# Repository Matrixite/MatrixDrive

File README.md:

# MatrixDrive

MatrixDrive started with a simple idea: make a Mega Drive/Genesis cartridge
that you can plug into a computer with USB-C, copy a game onto like a flash
drive, and then use in a real console.

Revision B takes that idea quite a bit further. It is also designed to run
Master System software on compatible Mega Drive hardware, supply ROM data to a
real 32X, work in the upper slot of Sonic & Knuckles, and keep supported save
data in battery-free FRAM.

- [Download the current source and prebuilt firmware package](https://github.com/Matrixite/MatrixDrive/raw/refs/heads/main/MatrixDrive_Dual_System_Cart_RevB_LockOn_Codemasters_64K_FRAM.zip)
- [Download the standalone KiCad project](https://github.com/Matrixite/MatrixDrive/raw/refs/heads/main/MatrixDrive_RevB_KiCad_Project.zip)

> [!IMPORTANT]
> MatrixDrive is still an engineering prototype. The software and logic have
> been tested, and the PCB has a preliminary fully connected route, but no
> physical cartridge has been built or tested in a console. Several package pin
> assignments still need to be verified and the board has not passed KiCad DRC.
> Please do not send the current PCB straight to a manufacturer.

## What MatrixDrive can do

| Mode | Files | Maximum size | What happens |
| --- | --- | ---: | --- |
| Mega Drive / Genesis | `.BIN`, `.MD`, `.GEN` | 4 MiB | The game is presented as linear cartridge ROM |
| 32X with real 32X hardware | `.32X` | 4 MiB | MatrixDrive supplies the ROM while the real 32X provides the 32X hardware |
| Sonic & Knuckles upper slot | Mega Drive images | 2 MiB recommended | Supports Sonic 2 lock-on and Sonic 3 with its dedicated save area |
| Master System | `.SMS` | 2 MiB | Uses either the Sega or Codemasters mapper selected by SW4 |

Master System mode should work on standard Mega Drive/Genesis Model 1 and Model
2 consoles. It will not work on an unmodified Genesis 3 or Sega Nomad because
their cartridge-port Master System mode pin is disconnected. The JVC X'Eye can
run SMS cartridges through an adapter, but its reset circuit prevents SMS games
from running from a Genesis flash cartridge such as MatrixDrive. Compatibility
with other all-in-one, portable, licensed, or clone systems has not yet been
verified. MatrixDrive also does not fit a standalone Master System cartridge
slot, and SMS mode cannot run through a 32X or the Sonic & Knuckles upper slot.

## How it works

When MatrixDrive is connected to a computer, it appears as a FAT16 drive called
`MATRIXDRV`. The RP2350B checks the game image and programs it into parallel NOR
flash. After USB is disconnected, the CPLD takes over and responds to the
console immediately, without waiting for the microcontroller to boot.

The main hardware is:

- an RP2350B for USB, file handling, validation, and flash programming;
- 32-Mbit x16 parallel NOR flash for predictable cartridge ROM reads;
- an ATF1508ASV CPLD for mode selection, address decoding, and SMS mapping;
- level translators and bus isolation for the 5 V console and 3.3 V logic;
- two FRAM devices providing 64 KiB of battery-free SMS save storage;
- a separate FRAM for the 8 KiB Sonic 3 lock-on save window;
- USB/console power isolation, status LEDs, SWD/UART, and test points.

## Loading a game

1. Remove MatrixDrive from the console, 32X, or lock-on cartridge.
2. Connect it to your computer with USB-C.
3. Open the `MATRIXDRV` drive, delete the old game, and copy over one supported
   image.
4. Safely eject the drive and wait for the green completion light.
5. Disconnect USB completely.
6. With all power off, select MD or SMS with SW2 and choose the required profile
   with SW4.
7. Insert the cartridge, then power on the console.

> [!WARNING]
> Never connect USB while MatrixDrive is fitted to a console, 32X, or Sonic &
> Knuckles cartridge. Never move SW2 or SW4 while powered, and never hot-plug any
> part of the cartridge stack.

## Switch settings

SW4 changes purpose depending on the position of SW2:

| SW2 | SW4 low | SW4 high |
| --- | --- | --- |
| MD | Linear ROM, 32X, or Sonic 2 lock-on | Linear ROM with Sonic 3 save FRAM |
| SMS | Sega mapper | Codemasters mapper |

Always change these switches with USB and console power disconnected.

## Sonic & Knuckles lock-on

For **Sonic 2 & Knuckles**, copy a normal Sonic 2 image, set SW2 to **MD**, and
set SW4 low to **LINEAR**. Power-of-two images up to 2 MiB are mirrored across
the upper-cartridge ROM window.

For **Sonic 3 & Knuckles**, copy a normal Sonic 3 image, set SW2 to **MD**, and
set SW4 high to **S3 SAVE**. MatrixDrive then maps the dedicated save FRAM over
odd-byte addresses `$200001-$203FFF` while leaving the rest of the ROM visible.

Read [Sonic & Knuckles lock-on mode](MatrixDrive_Dual_System_Cart_RevB/docs/sonic-knuckles-lock-on.md)
for the exact mapping, switch positions, and physical-fit checks.

## Using a real 32X

MatrixDrive is not trying to reproduce a 32X. A real 32X still supplies its
processors, boot ROM, registers, video, and audio hardware; MatrixDrive only
supplies the cartridge ROM.

Copy a `.32X` image, set SW2 to **MD**, leave SW4 low, disconnect USB, and fit
MatrixDrive to an unpowered 32X. The installer checks the `SEGA` header and
`MARS CHECK MODE` marker before accepting the image.

Do not use SW4 high for 32X software because that setting deliberately replaces
part of the ROM address range with the Sonic 3 save window. More detail is in
[32X cartridge mode](MatrixDrive_Dual_System_Cart_RevB/docs/32x-mode.md).

## Master System mapping and saves

| Profile | Mapper writes | Starting ROM banks | Save window |
| --- | --- | --- | --- |
| Sega | `$FFFC-$FFFF` | 0, 1, 2 | 16 KiB at `$8000-$BFFF` |
| Codemasters | `$0000`, `$4000`, `$8000` | 0, 1, 0 | 8 KiB at `$A000-$BFFF` |

In Codemasters mode, bit 7 of the `$4000` write enables FRAM and bits 2:0 choose
one of eight 8 KiB banks. This makes all 64 KiB of SMS save storage available
without hiding the ROM at `$8000-$9FFF`.

See [Master System mode](MatrixDrive_Dual_System_Cart_RevB/docs/master-system-mode.md)
for the full register and banking behaviour.

## Supported image rules

- Mega Drive/Genesis images must be normal big-endian ROMs, contain `SEGA` at
  offset `0x100`, and fit within 4 MiB.
- 32X images must use `.32X`, contain `SEGA` at `0x100` and `MARS CHECK MODE` at
  `0x3C0`, be a multiple of four bytes, and fit within 4 MiB.
- Lock-on images should be even-sized powers of two no larger than 2 MiB.
- Headerless SMS images need `TMR SEGA` at `0x1FF0`, `0x3FF0`, or `0x7FF0`.
- Interleaved `.SMD` files and copier headers are not supported.
- Only use game images that you are legally entitled to use.

No commercial ROM images are included in this repository.

## What has been tested

The project is automatically rebuilt and tested on every change. The passing
software-only tests currently cover:

- the FAT16 USB drive and ROM installer;
- Mega Drive, Master System, and 32X image validation;
- simulated NOR programming and ROM mirroring;
- Sega and Codemasters SMS mapper behaviour;
- Codemasters FRAM enabling and all eight save banks;
- Sonic 2/Sonic 3 lock-on mapping and the Sonic 3 save decoder;
- CPLD RTL simulation for MD, SMS, 32X ROM access, and lock-on modes;
- a complete RP2350B firmware build;
- a two-ROM emulator test that reached the combined Sonic 3 & Knuckles title
  screen and opening sequence.

These tests show that the intended software and logic paths behave correctly.
They cannot prove cartridge fit, signal timing, voltage translation, power
isolation, save retention, or operation on real Sega hardware.

## PCB status

The KiCad project contains a complete logical schematic and a preliminary
eight-layer PCB route. The routing report currently records all 188 routable
nets connected, using six signal layers plus dedicated ground and 3.3 V planes.

Before a board can be considered ready to build, it still needs:

- verified physical pin assignments and manufacturer footprints for the
  RP2350B, CPLD, NOR, translators, and FRAM devices;
- CPLD fitting, resource checks, and worst-case timing analysis;
- KiCad ERC/DRC after refilling the copper zones;
- USB differential-pair and signal/power-integrity review;
- cartridge-edge, PCB-thickness, bevel, shell, and insertion measurements;
- staged bench testing before it is connected to any console.

Only the Sonic 3 odd-byte save layout is implemented for Mega Drive software.
Generic Mega Drive or 32X SRAM/EEPROM saves, ROMs larger than 4 MiB,
enhancement hardware, unusual regional or game-specific SMS mappers, light-gun
support, and Sega mapper RAM-at-`$C000` mode are outside this revision.

Start with [Safety and bring-up](MatrixDrive_Dual_System_Cart_RevB/docs/safety-and-bringup.md)
before attempting any hardware test.

## Project layout

| Path | What you will find there |
| --- | --- |
| [`MatrixDrive_Dual_System_Cart_RevB/`](MatrixDrive_Dual_System_Cart_RevB/) | Main Revision B project |
| [`cpld/`](MatrixDrive_Dual_System_Cart_RevB/cpld/) | Mapper RTL, reference model, and testbench |
| [`firmware/`](MatrixDrive_Dual_System_Cart_RevB/firmware/) | RP2350B USB installer firmware |
| [`hardware/`](MatrixDrive_Dual_System_Cart_RevB/hardware/) | KiCad files, BOM, pinout, netlist, and routing report |
| [`docs/`](MatrixDrive_Dual_System_Cart_RevB/docs/) | Architecture, compatibility, and bring-up notes |
| [`tools/`](MatrixDrive_Dual_System_Cart_RevB/tools/) | Project generator, router, and validation scripts |

The [full design README](MatrixDrive_Dual_System_Cart_RevB/README.md) contains
the component-level details and additional design notes.

## Building and testing the project

You will need Python 3, the Raspberry Pi Pico SDK 2.3.0, an Arm GNU toolchain,
CMake/Ninja, and Icarus Verilog.

```sh
cd MatrixDrive_Dual_System_Cart_RevB
python3 tools/generate_kicad_project.py
python3 tools/route_kicad_pcb.py
python3 tools/validate_project.py
```

To build the RP2350B firmware:

```sh
export PICO_SDK_PATH=/absolute/path/to/pico-sdk
cmake -S firmware -B ../build/firmware -G Ninja \
  -DPICO_BOARD=matrixdrive \
  -DPICO_PLATFORM=rp2350-arm-s \
  -DCMAKE_BUILD_TYPE=Release
cmake --build ../build/firmware
```

## Technical references

- [Genesis Plus GX cartridge implementation](https://github.com/ekeeke/Genesis-Plus-GX/blob/master/core/cart_hw/md_cart.c)
- [Sega 32X Hardware Manual transcription](https://github.com/matiaszanolli/sega-vr-disasm/blob/master/docs/32x-hardware-manual.md)
- [Raspberry Pi RP2350 documentation](https://www.raspberrypi.com/documentation/microcontrollers/microcontroller-chips.html)
- [Microchip ATF1508ASV](https://www.microchip.com/en-us/product/atf1508asv)
- [Infineon FM18W08 FRAM](https://www.infineon.com/part/FM18W08-SG)
- [TI SN74LVC1T45](https://www.ti.com/product/SN74LVC1T45)

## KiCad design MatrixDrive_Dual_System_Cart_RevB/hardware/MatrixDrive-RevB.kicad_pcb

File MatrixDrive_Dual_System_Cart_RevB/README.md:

# MatrixDrive Dual-System USB Cartridge — Revision B

MatrixDrive Revision B is a prototype USB-loadable Mega Drive/Genesis cartridge that can also supply ROM to a real 32X, run Master System software on compatible consoles, and act as the upper cartridge in Sonic & Knuckles lock-on mode. USB-C exposes a removable FAT16 drive named `MATRIXDRV`; after one ROM is copied and safely ejected, the RP2350B installs it into non-volatile parallel NOR.

Console reads never depend on RP2350 response time. Translators and an instant-on CPLD connect the console directly to NOR or the selected FRAM.

## Supported images

| Console mode | File | Active image limit | Cartridge hardware |
| --- | --- | ---: | --- |
| Mega Drive / Genesis | `.BIN`, `.MD`, `.GEN` | 4 MiB | Linear `$000000-$3FFFFF` ROM |
| 32X through a real 32X | `.32X` | 4 MiB | Linear x16 ROM with 4 MiB mask-ROM-style mirroring |
| Sonic & Knuckles upper slot | Mega Drive image | 2 MiB recommended | Mirrored ROM; optional Sonic 3 save profile |
| Master System | `.SMS` | 2 MiB | Sega or Codemasters mapper selected by SW4 |

Power-of-two Mega Drive images smaller than 2 MiB are repeated by the installer through the full 2 MiB lock-on window. This gives a 1 MiB Sonic 2 image the mirroring expected from its original mask ROM.

Power-of-two `.32X` images smaller than 4 MiB are repeated through the complete 32-Mbit cartridge space. The firmware requires the standard `SEGA` header at `0x100` and `MARS CHECK MODE` at `0x3C0`, then preserves every ROM byte—including the mandatory 32X security/startup area beginning at `0x3F0`.

For Sonic 3 & Knuckles, SW4's high position in MD mode enables a dedicated 8 KiB odd-byte FRAM window at `$200001-$203FFF`. This storage is physically separate from the two FM18W08 devices that supply the complete 64 KiB SMS save array.

SMS images are stored one byte per x16 NOR word. The CPLD implements Sega or Codemasters 16 KiB banking selected by SW4. Plain 8/16/32/48 KiB images and larger mapped images work.

## Normal use

1. Remove MatrixDrive from the console, 32X, or Sonic & Knuckles cartridge.
2. Connect USB-C, remove the previous image, and copy one supported ROM to `MATRIXDRV`.
3. Safely eject and wait for the steady green completion indication.
4. Disconnect USB and set SW2/SW4 while all hardware is unpowered.
5. Insert MatrixDrive directly into the console, into the real 32X cartridge slot for `.32X` use, or into the Sonic & Knuckles upper slot for MD lock-on use.
6. Power on. In SMS mode, use the cartridge PAUSE button when a game needs the Master System NMI pause input.

### Switch positions

| Use | SW2 | SW4 |
| --- | --- | --- |
| Normal Mega Drive or Sonic 2 & Knuckles | MD | Low: LINEAR |
| 32X cartridge through real 32X hardware | MD | Low: LINEAR |
| Sonic 3 & Knuckles with saves | MD | High: S3 SAVE |
| Sega-mapper SMS | SMS | Low: SEGA |
| Codemasters-mapper SMS | SMS | High: CODEMASTERS |

Never move either switch while powered. Never connect USB while MatrixDrive is inserted into a console, 32X, or another cartridge.

## 32X compatibility

MatrixDrive does not emulate a 32X. In this mode, the physical 32X supplies its dual SH2 processors, boot ROM, registers, video and audio hardware, while MatrixDrive behaves as the attached 4 MiB cartridge ROM. The 32X adapter performs its normal cartridge banking internally.

Use SW2=MD and SW4=LINEAR. SW4's S3 SAVE position is not compatible because it intentionally replaces odd-byte addresses `$200001-$203FFF` with FRAM. Generic 32X SRAM/EEPROM saves, images larger than 4 MiB, and special cartridge hardware are not implemented.

See `docs/32x-mode.md` for exact mapping and real-hardware bring-up requirements.

## Lock-on compatibility

The electrical profile follows the documented lock-on behaviour and the Genesis Plus GX implementation:

- Sonic & Knuckles supplies its own ROM at the lower 2 MiB and exposes the upper cartridge in the remaining window.
- MatrixDrive behaves as a normal MD ROM in the upper slot.
- The installer supplies mask-ROM-style mirroring for even-sized power-of-two images up to 2 MiB.
- The Sonic 3 save profile maps U20 to odd-byte addresses `$200001-$203FFF`.
- U19 translates the CPLD's high-byte-disable request into the 5 V domain so U7 is inactive during low-byte-only save cycles.
- Sonic & Knuckles owns its `$A130F0` lock-on control; MatrixDrive does not emulate the base lock-on cartridge.

See `docs/sonic-knuckles-lock-on.md` for exact use and remaining physical-fit validation.

## Image validation

- Mega Drive images require `SEGA` at byte offset `0x100`, normal big-endian byte order, and a maximum size of 4 MiB. Interleaved `.SMD` images are rejected.
- `.32X` images must be a multiple of four bytes, fit in 4 MiB, contain `SEGA` at `0x100`, and contain `MARS CHECK MODE` at `0x3C0`.
- Lock-on images should be even-sized powers of two no larger than 2 MiB.
- Headerless SMS images require `TMR SEGA` at `0x1FF0`, `0x3FF0`, or `0x7FF0`.
- Use only software you are legally entitled to use.

## Hardware summary

- RP2350B, USB Full-Speed Mass Storage, and a 16 MiB FAT16 staging flash.
- S29GL032N-compatible 32-Mbit x16 active parallel NOR.
- ATF1508ASV-15AU100 CPLD for instant-on mode, SMS mapping, and Sonic 3 save decode.
- U17/U18: two FM18W08 32 KiB x8 FRAMs, exactly 64 KiB for SMS saves.
- U20: dedicated FM18W08, with 8 KiB decoded for Sonic 3 lock-on saves.
- U19: SN74LVC1T45 translating the MD high-data-disable control to CART_5V.
- Dual-supply 5 V/3.3 V translation on every active cartridge signal.
- USB/console source isolation, PROGRAM and PAUSE buttons, and power-off selectors.

## Project contents

- `docs/architecture.md` — electrical and data-path architecture.
- `docs/master-system-mode.md` — SMS mapper and storage details.
- `docs/32x-mode.md` — real-32X cartridge mapping, switches, limits, and bring-up.
- `docs/sonic-knuckles-lock-on.md` — lock-on mapping, switches, fit, and limitations.
- `docs/safety-and-bringup.md` — mandatory staged test procedure.
- `hardware/bom.csv`, `connector-pinout.csv`, `electrical-netlist.csv` — connection authorities.
- `hardware/MatrixDrive-RevB.sch` — complete logical schematic; KiCad 8/9 converts it to native format on first save.
- `hardware/MatrixDrive-RevB.kicad_pcb` — native preliminary routed eight-layer PCB with the physical cartridge edge, six signal layers, and dedicated ground/3.3 V planes.
- `hardware/routing-report.json` — deterministic route completion counts, layer assignment, widths, and via dimensions.
- `hardware/README-KICAD.md` — project opening instructions and fabrication release gates.
- `cpld/matrixdrive_mapper.v` — synthesizable SMS and lock-on decoder RTL.
- `cpld/test_matrixdrive_mapper.v` — RTL mapper/FRAM testbench.
- `firmware/` — RP2350/Pico SDK firmware source.

## Engineering status

This is a **Revision B engineering prototype**, not a fabrication-ready or production-tested commercial cartridge. The PCB has a preliminary connectivity-complete route, but it has not passed KiCad DRC or physical review. Before fabrication, review and verify the logical schematic, assign and fit the CPLD, verify resources and timing, copy the official RP2350B minimal design, confirm exact package pin maps, review/refine the route, pass ERC/DRC, and measure the edge/shell against a normal donor cartridge, a real 32X cartridge slot, and a real Sonic & Knuckles upper slot.

Do not send the included KiCad PCB directly to fabrication. Complete the release gates in `hardware/README-KICAD.md` and `docs/safety-and-bringup.md` before any console test.

The repository root also contains `MatrixDrive_RevB_KiCad_Project.zip`, a
standalone copy of the schematic, board, symbol library, BOM and connection
authorities.

## Build prerequisites

- Raspberry Pi Pico SDK 2.3.0 and Arm GNU Toolchain.
- CMake plus Ninja or Make.
- Icarus Verilog for RTL simulation.
- KiCad 8 or later for schematic conversion, PCB editing, ERC and DRC.
- A verified ATF1508ASV fitting/JED programming flow.

The prototype USB descriptor uses TinyUSB's development VID `0xCAFE`. Obtain a proper VID/PID before distribution.

## Primary references

- Genesis Plus GX MD cartridge: <https://github.com/ekeeke/Genesis-Plus-GX/blob/master/core/cart_hw/md_cart.c>
- Genesis Plus GX SRAM: <https://github.com/ekeeke/Genesis-Plus-GX/blob/master/core/cart_hw/sram.c>
- Sega 32X Hardware Manual transcription: <https://github.com/matiaszanolli/sega-vr-disasm/blob/master/docs/32x-hardware-manual.md>
- TI SN74LVC1T45: <https://www.ti.com/product/SN74LVC1T45>
- RP2350: <https://www.raspberrypi.com/documentation/microcontrollers/microcontroller-chips.html>
- ATF1508ASV: <https://www.microchip.com/en-us/product/atf1508asv>
- FM18W08 FRAM: <https://www.infineon.com/part/FM18W08-SG>

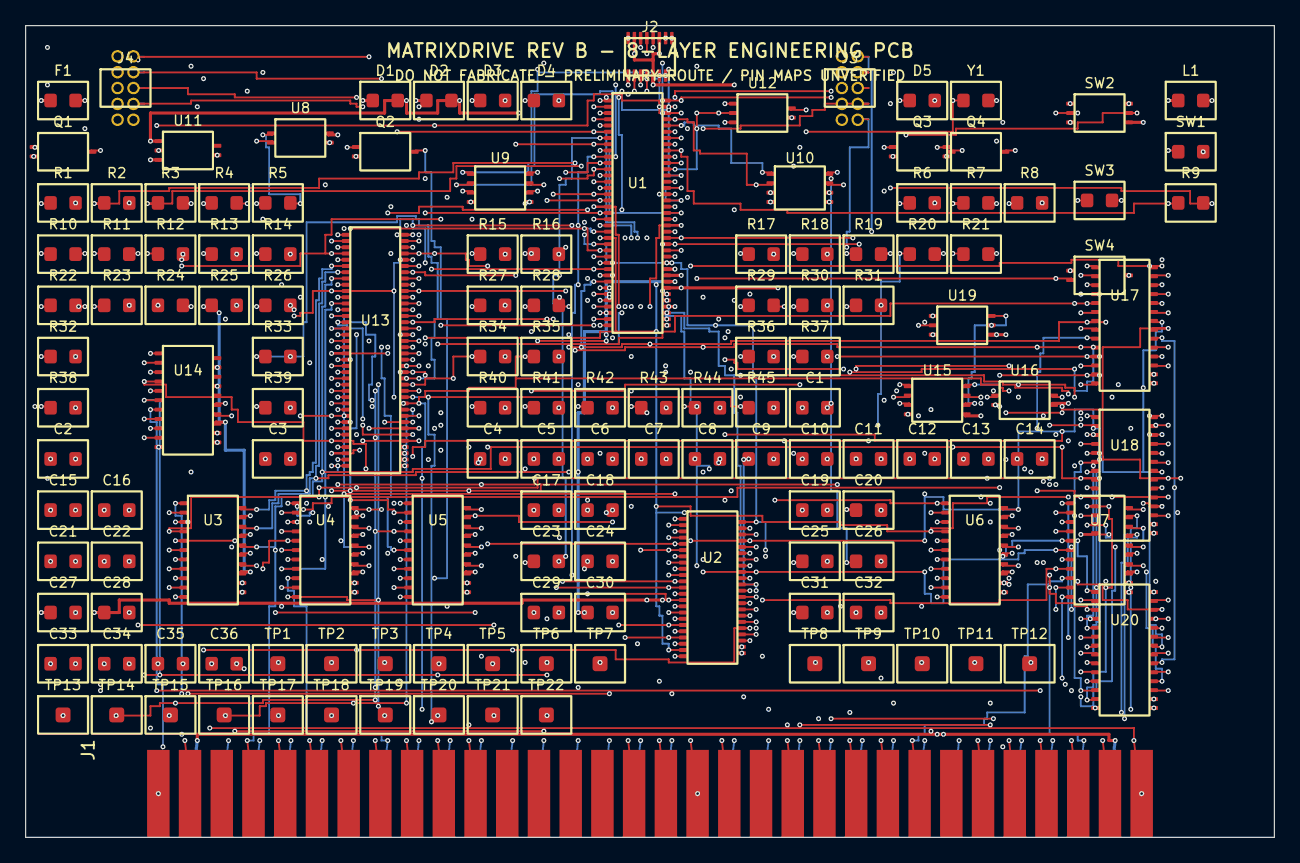
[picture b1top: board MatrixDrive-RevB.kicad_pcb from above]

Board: 8 copper layers, 100.0 x 65.0 mm, 143 parts (0 on the bottom side), 190 nets.

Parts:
C1, C2, C3, C4, C5, C6, C7, C8, C9, C10, C11, C12, C13, C14, C15, C16, C17, C18, C34, C35, C36: 100nF; 0603
C19, C20, C21, C22: 1uF; 0603
C23, C24: 10uF; 0805
C25, C26: 15pF; 0402
C27: 4.7uF; 0603
C28, C29, C30, C31, C32, C33: TBD_REF; 0402
D1, D2: PMEG2010AEB; SOD_523
D3: GREEN_LED; 0603_LED
D4: AMBER_LED; 0603_LED
D5: RED_LED; 0603_LED
F1: MF-MSMF020-2; 1812
J1: MEGA_DRIVE_EDGE; MD_2x32_EDGE
J2: USB4105-GF-A; USB_C_16P
J3: SWD_UART_2x5 DNP; HDR_2x5_1_27
J4: CPLD_JTAG_2x5; HDR_2x5_1_27
L1: 3.3uH; 2016
Q1, Q2, Q3, Q4: 2N7002; SOT_23
R1, R2: 5.1k; 0603
R3, R4: 27R; 0603
R5, R12, R19, R20, R21, R22, R23, R25, R26, R27, R31, R32, R33, R34, R35, R36, R42, R43, R45: 10k; 0603
R6, R7, R8, R14, R29, R30, R37, R38, R39, R40, R41, R44: 100k; 0603
R9, R10, R11, R28: 1k; 0603
R13: 0R; 0603
R15, R16, R17, R18: 10k DNP; 0603
R24: 33R; 0603
SW1: PROGRAM; SW_2P
SW2: MD_SMS_DPDT; SW_DPDT_6P
SW3: SMS_PAUSE; SW_2P
SW4: PROFILE_SPDT; SW_SPDT_3P
TP1: CART_5V; TP_SMD_1MM
TP2: USB_VBUS; TP_SMD_1MM
TP3: SYS_5V; TP_SMD_1MM
TP4: 3V3; TP_SMD_1MM
TP5: GND; TP_SMD_1MM
TP6: BUS_DISABLE; TP_SMD_1MM
TP7: SMS_MODE_3V3; TP_SMD_1MM
TP8: SMS_MODE_5V; TP_SMD_1MM
TP9: USB_MODE_3V3; TP_SMD_1MM
TP10: ROM_CE_N; TP_SMD_1MM
TP11: ROM_OE_N; TP_SMD_1MM
TP12: ROM_WE_N; TP_SMD_1MM
TP13: FRAM_CE_N; TP_SMD_1MM
TP14: FRAM_HI_CE_N; TP_SMD_1MM
TP15: FRAM_OE_N; TP_SMD_1MM
TP16: FRAM_WE_N; TP_SMD_1MM
TP17: MD_FRAM_CE_N; TP_SMD_1MM
TP18: MD_HIGH_DISABLE_3V3; TP_SMD_1MM
TP19: LWR_3V3; TP_SMD_1MM
TP20: UWR_3V3; TP_SMD_1MM
TP21: AS_3V3; TP_SMD_1MM
TP22: TIME_3V3; TP_SMD_1MM
U1: RP2350B; UNVERIFIED_LOGICAL_PACKAGE
U2: S29GL032N90TFI040; TSOP_I_48_UNVERIFIED_PINMAP
U3, U4, U5, U6, U7, U14: SN74LVC8T245PWR; TSSOP_24_LOGICAL
U8: SN74LVC1G17DBVR; SOT_23_5
U9: W25Q16JVSSIQ; SOIC_8
U10: W25Q128JVSIQ; SOIC_8
U11: TLV75533PDBVR; SOT_23_5
U12: TPD2EUSB30DRTR; DRT_9_LOGICAL
U13: ATF1508ASV-15AU100; TQFP_100_UNASSIGNED
U15: SN74LVC2G32DCUR; VSSOP_8
U16: SN74LVC1G04DBVR; SOT_23_5
U17, U18, U20: FM18W08-SG; SOIC_28_LOGICAL
U19: SN74LVC1T45DBVR; SOT_23_6
Y1: 12MHz_CRYSTAL; 3225_4P

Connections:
1V1: C27.1, C28.1, L1.2, U1.DVDD, U1.VREG_FB
3V3: C1.1, C2.1, C3.1, C4.1, C5.1, C6.1, C7.1, C8.1, C9.1, C10.1, C11.1, C12.1, C13.1, C14.1, C15.1, C16.1, C17.1, C18.1, C19.1, C21.1, C22.1, C24.1, C29.1, C32.1, C33.1, C34.1, C35.1, C36.1, J3.1, J4.1, R12.2, R24.1, R25.2, R26.2, R27.2, R31.2, R32.2, R34.2, R35.2, R36.2, R43.2, R45.2, SW2.3, SW4.3, TP4.1, U1.IOVDD_1, U1.IOVDD_2, U1.VREG_IN, U2.VCC, U3.VCCB, U4.VCCB, U5.VCCB, U6.VCCB, U7.VCCB, U9.8, U10.3, U10.7, U10.8, U11.5, U13.VCC_1, U13.VCC_2, U14.VCCB, U17.VDD, U18.VDD, U19.1, U19.5, U20.VDD
ADC_AVDD: C31.1, U1.ADC_AVDD
AS_3V3: TP21.1, U14.B4
AS_N: J1.B18, U14.A4
BOOT_QSPI_CS: U1.QSPI_CS, U9.1
BOOT_QSPI_IO0: U1.QSPI_SD0, U9.5
BOOT_QSPI_IO1: U1.QSPI_SD1, U9.2
BOOT_QSPI_IO2: U1.QSPI_SD2, U9.3
BOOT_QSPI_IO3: U1.QSPI_SD3, U9.7
BOOT_QSPI_SCK: U1.QSPI_SCLK, U9.6
BUS_DISABLE: R14.1, R15.1, R16.1, R17.1, R18.1, TP6.1, U3.OE_N, U4.OE_N, U5.OE_N, U6.OE_N, U8.Y, U14.OE_N, U15.1
CART_5V: C20.1, D1.1, F1.2, R19.2, R20.2, R21.2, R22.2, SW2.6, TP1.1, U3.VCCA, U4.VCCA, U5.VCCA, U6.VCCA, U7.VCCA, U8.VCC, U14.VCCA, U15.8, U16.5, U19.6
CART_5V_IN: F1.1, J1.A2, J1.A31
CART_A0: U3.B1, U13.CART_A0, U17.A0, U18.A0, U20.A0
CART_A1: U3.B2, U13.CART_A1, U17.A1, U18.A1, U20.A1
CART_A2: U3.B3, U13.CART_A2, U17.A2, U18.A2, U20.A2
CART_A3: U3.B4, U13.CART_A3, U17.A3, U18.A3, U20.A3
CART_A4: U3.B5, U13.CART_A4, U17.A4, U18.A4, U20.A4
CART_A5: U3.B6, U13.CART_A5, U17.A5, U18.A5, U20.A5
CART_A6: U3.B7, U13.CART_A6, U17.A6, U18.A6, U20.A6
CART_A7: U3.B8, U13.CART_A7, U17.A7, U18.A7, U20.A7
CART_A8: U4.B1, U13.CART_A8, U17.A8, U18.A8, U20.A8
CART_A9: U4.B2, U13.CART_A9, U17.A9, U18.A9, U20.A9
CART_A10: U4.B3, U13.CART_A10, U17.A10, U18.A10, U20.A10
CART_A11: U4.B4, U13.CART_A11, U17.A11, U18.A11, U20.A11
CART_A12: U4.B5, U13.CART_A12, U17.A12, U18.A12, U20.A12
CART_A13: U4.B6, U13.CART_A13
CART_A14: U4.B7, U13.CART_A14
CART_A15: U4.B8, U13.CART_A15
CART_A16: U5.B1, U13.CART_A16
CART_A17: U5.B2, U13.CART_A17
CART_A18: U5.B3, U13.CART_A18
CART_A19: U5.B4, U13.CART_A19
CART_A20: U5.B5, U13.CART_A20
CART_N: J1.B32, R13.1
CAS0_3V3: U5.B7, U13.CAS0_N
CAS0_N: J1.B16, U5.A7
CAS2_3V3: U5.B8, U13.CAS2_N
CAS2_N: J1.B21, U5.A8
CC1: J2.A5, R1.1
CC2: J2.B5, R2.1
CE0_3V3: U5.B6, U13.CE0_N
CE0_N: J1.B17, U5.A6
CPLD_TCK: J4.4, U13.TCK
CPLD_TDI: J4.8, U13.TDI
CPLD_TDO: J4.6, U13.TDO
CPLD_TMS: J4.2, U13.TMS
DATA_HIGH_BASE_DISABLE: U15.3, U15.6
DATA_HIGH_DISABLE: U7.OE_N, U15.5
FRAM_A13: R42.1, U13.FRAM_A13, U17.A13, U18.A13
FRAM_A14: R33.1, U13.FRAM_A14, U17.A14, U18.A14
FRAM_CE_N: R34.1, TP13.1, U13.FRAM_CE_N, U17.CE_N
FRAM_HI_CE_N: R43.1, TP14.1, U13.FRAM_HI_CE_N, U18.CE_N
FRAM_OE_N: R35.1, TP15.1, U13.FRAM_OE_N, U17.OE_N, U18.OE_N, U20.OE_N
FRAM_WE_N: R36.1, TP16.1, U13.FRAM_WE_N, U17.WE_N, U18.WE_N, U20.WE_N
GND: C1.2, C2.2, C3.2, C4.2, C5.2, C6.2, C7.2, C8.2, C9.2, C10.2, C11.2, C12.2, C13.2, C14.2, C15.2, C16.2, C17.2, C18.2, C19.2, C20.2, C21.2, C22.2, C23.2, C24.2, C25.2, C26.2, C27.2, C28.2, C29.2, C30.2, C31.2, C32.2, C33.2, C34.2, C35.2, C36.2, D3.2, D4.2, D5.2, J1.A1, J1.A18, J1.A32, J2.A1, J2.A12, J2.B1, J2.B12, J2.S1, J3.3, J3.5, J3.9, J4.3, J4.5, J4.9, Q1.2, Q2.2, Q3.2, Q4.2, R1.2, R2.2, R6.2, R8.2, R13.2, R14.2, R15.2, R16.2, R17.2, R18.2, R23.2, R30.2, R33.2, R37.2, R38.2, R39.2, R40.2, R41.2, R42.2, R44.2, SW1.2, SW2.1, SW2.4, SW4.1, TP5.1, U1.EP, U1.GND_1, U1.GND_2, U2.GND, U3.GND, U4.GND, U5.GND, U6.GND, U7.GND, U8.GND, U9.4, U10.4, U11.2, U12.GND, U13.GND_1, U13.GND_2, U14.A6, U14.A7, U14.A8, U14.GND, U15.4, U16.2, U17.VSS, U18.VSS, U19.3, U20.A13, U20.A14, U20.VSS
LED_AMBER: R10.1, U1.GPIO46
LED_AMBER_A: D4.1, R10.2
LED_GREEN: R9.1, U1.GPIO45
LED_GREEN_A: D3.1, R9.2
LED_RED: R11.1, U1.GPIO47
LED_RED_A: D5.1, R11.2
LOW_DATA_DIR: U6.DIR, U16.4
LWR_3V3: TP19.1, U13.LWR_N, U14.B1
LWR_N: J1.B28, U14.A1, U16.1
M3_N: J1.B30, Q1.3
MD_FRAM_CE_N: R45.1, TP17.1, U13.MD_FRAM_CE_N, U20.CE_N
MD_HIGH_DISABLE_3V3: TP18.1, U13.MD_HIGH_DISABLE, U19.2
MD_HIGH_DISABLE_5V: U15.7, U19.4
MEM_D0: U1.GPIO21, U2.DQ0, U6.B1, U13.DATA_IN0, U17.DQ0, U18.DQ0, U20.DQ0
MEM_D1: U1.GPIO22, U2.DQ1, U6.B2, U13.DATA_IN1, U17.DQ1, U18.DQ1, U20.DQ1
MEM_D2: U1.GPIO23, U2.DQ2, U6.B3, U13.DATA_IN2, U17.DQ2, U18.DQ2, U20.DQ2
MEM_D3: U1.GPIO24, U2.DQ3, U6.B4, U13.DATA_IN3, U17.DQ3, U18.DQ3, U20.DQ3
MEM_D4: U1.GPIO25, U2.DQ4, U6.B5, U13.DATA_IN4, U17.DQ4, U18.DQ4, U20.DQ4
MEM_D5: U1.GPIO26, U2.DQ5, U6.B6, U13.DATA_IN5, U17.DQ5, U18.DQ5, U20.DQ5
MEM_D6: U1.GPIO27, U2.DQ6, U6.B7, U13.DATA_IN6, U17.DQ6, U18.DQ6, U20.DQ6
MEM_D7: U1.GPIO28, U2.DQ7, U6.B8, U13.DATA_IN7, U17.DQ7, U18.DQ7, U20.DQ7
MEM_D8: U1.GPIO29, U2.DQ8, U7.B1
MEM_D9: U1.GPIO30, U2.DQ9, U7.B2
MEM_D10: U1.GPIO31, U2.DQ10, U7.B3
MEM_D11: U1.GPIO32, U2.DQ11, U7.B4
MEM_D12: U1.GPIO33, U2.DQ12, U7.B5
MEM_D13: U1.GPIO34, U2.DQ13, U7.B6
MEM_D14: U1.GPIO35, U2.DQ14, U7.B7
MEM_D15: U1.GPIO36, U2.DQ15, U7.B8
MRES_3V3: R41.1, U13.RESET_N, U14.B2
MRES_N: J1.B2, U14.A2
PAUSE_GATE: Q4.1, R40.1, SW3.2
ROM_A0: U1.GPIO0, U2.A0, U13.ROM_A0
ROM_A1: U1.GPIO1, U2.A1, U13.ROM_A1
ROM_A2: U1.GPIO2, U2.A2, U13.ROM_A2
ROM_A3: U1.GPIO3, U2.A3, U13.ROM_A3
ROM_A4: U1.GPIO4, U2.A4, U13.ROM_A4
ROM_A5: U1.GPIO5, U2.A5, U13.ROM_A5
ROM_A6: U1.GPIO6, U2.A6, U13.ROM_A6
ROM_A7: U1.GPIO7, U2.A7, U13.ROM_A7
ROM_A8: U1.GPIO8, U2.A8, U13.ROM_A8
ROM_A9: U1.GPIO9, U2.A9, U13.ROM_A9
ROM_A10: U1.GPIO10, U2.A10, U13.ROM_A10
ROM_A11: U1.GPIO11, U2.A11, U13.ROM_A11
ROM_A12: U1.GPIO12, U2.A12, U13.ROM_A12
ROM_A13: U1.GPIO13, U2.A13, U13.ROM_A13
ROM_A14: U1.GPIO14, U2.A14, U13.ROM_A14
ROM_A15: U1.GPIO15, U2.A15, U13.ROM_A15
ROM_A16: U1.GPIO16, U2.A16, U13.ROM_A16
ROM_A17: U1.GPIO17, U2.A17, U13.ROM_A17
ROM_A18: U1.GPIO18, U2.A18, U13.ROM_A18
ROM_A19: U1.GPIO19, U2.A19, U13.ROM_A19
ROM_A20: U1.GPIO20, U2.A20, U13.ROM_A20
ROM_BYTE_N: R27.1, U2.BYTE_N
ROM_CE_N: R31.1, TP10.1, U1.GPIO37, U2.CE_N, U13.ROM_CE_N
ROM_OE_N: R32.1, TP11.1, U1.GPIO38, U2.OE_N, U13.ROM_OE_N
ROM_RESET_N: R25.1, U2.RESET_N
ROM_WE_N: R12.1, TP12.1, U1.GPIO39, U2.WE_N
ROM_WP_N: R26.1, U2.WP_N
RUN_N: J3.6, U1.RUN
SMS_MAPPER_CM_3V3: R44.1, SW4.2, U13.CODEMASTERS
SMS_MODE_3V3: Q1.1, Q2.1, Q3.1, R37.1, R38.1, R39.1, SW2.2, SW3.1, TP7.1, U13.SMS_MODE
SMS_MODE_5V: SW2.5, TP8.1, U15.2
STAGE_CS_N: U1.GPIO41, U10.1
STAGE_MISO: U1.GPIO40, U10.2
STAGE_MOSI: U1.GPIO43, U10.5
STAGE_SCK: U1.GPIO42, U10.6
SWCLK: J3.4, U1.SWCLK
SWDIO: J3.2, U1.SWDIO
SYS_5V: C23.1, D1.2, D2.2, TP3.1, U11.1, U11.3
TIME_3V3: TP22.1, U14.B5
TIME_N: J1.B31, U14.A5
U3_DIR: R19.1, U3.DIR
U4_DIR: R20.1, U4.DIR
U5_DIR: R21.1, U5.DIR
U7_DIR: R23.1, U7.DIR
U14_DIR: R22.1, U14.DIR
UART_RX: J3.10, U1.UART_RX
UART_TX: J3.8, U1.UART_TX
USB_DM: J2.A7, J2.B7, R4.1, U12.IO2A
USB_DM_MCU: R4.2, U1.USB_DM, U12.IO2B
USB_DP: J2.A6, J2.B6, R3.1, U12.IO1A
USB_DP_MCU: R3.2, U1.USB_DP, U12.IO1B
USB_MODE_3V3: R29.2, R30.1, TP9.1, U13.USB_MODE
USB_PRESENT: R5.2, R6.1, U8.A
USB_SENSE_PROGRAM: R7.2, R8.1, SW1.1, U1.GPIO44
USB_VBUS: D2.1, J2.A4, J2.A9, J2.B4, J2.B9, R5.1, R7.1, R29.1, TP2.1
UWR_3V3: TP20.1, U14.B3
UWR_N: J1.B29, U14.A3
VA1: J1.A17, U3.A1
VA2: J1.A15, U3.A2
VA3: J1.A13, U3.A3
VA4: J1.A11, U3.A4
VA5: J1.A9, U3.A5
VA6: J1.A7, U3.A6
VA7: J1.A5, U3.A7
VA8: J1.A3, U3.A8
VA9: J1.B4, U4.A1
VA10: J1.B5, U4.A2
VA11: J1.A4, U4.A3
VA12: J1.A6, U4.A4
VA13: J1.A8, U4.A5
VA14: J1.A10, U4.A6
VA15: J1.A12, U4.A7
VA16: J1.A14, U4.A8
VA17: J1.A16, U5.A1
VA18: J1.B6, U5.A2
VA19: J1.B7, U5.A3
VA20: J1.B8, U5.A4
VA21: J1.B9, Q2.3, U5.A5
VA22: J1.B10, Q3.3
VA23_PAUSE: J1.B11, Q4.3
VD0: J1.A20, U6.A1
VD1: J1.A23, U6.A2
VD2: J1.A26, U6.A3
VD3: J1.A29, U6.A4
VD4: J1.A28, U6.A5
VD5: J1.A25, U6.A6
VD6: J1.A22, U6.A7
VD7: J1.A19, U6.A8
VD8: J1.A21, U7.A1
VD9: J1.A24, U7.A2
VD10: J1.A27, U7.A3
VD11: J1.A30, U7.A4
VD12: J1.B25, U7.A5
VD13: J1.B24, U7.A6
VD14: J1.B23, U7.A7
VD15: J1.B22, U7.A8
VREG_AVDD: C30.1, R24.2, U1.VREG_AVDD
VREG_SW: L1.1, U1.VREG_SW
XIN: R28.2, U1.XIN
XIN_XTAL: C25.1, R28.1, Y1.1
XOUT: C26.1, U1.XOUT, Y1.2

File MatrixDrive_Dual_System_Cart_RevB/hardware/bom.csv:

Reference,Quantity,Value or part,Description,Preferred footprint,Populate Rev B,Notes
U1,1,RP2350B,USB and flash controller,QFN-80-1EP 10x10mm,Yes,Use RP2350B for GPIO0-47
U2,1,S29GL032N90TFI040,32-Mbit 3V x16 parallel NOR,TSOP-I-48 18.4x12mm,Yes,90ns or faster; verify purchased package pinout
U3-U5,3,SN74LVC8T245PWR,Address and primary-control 5V-to-3V3 translators,TSSOP-24,Yes,DIR A to B
U6,1,SN74LVC8T245PWR,Low data byte bidirectional translator,TSSOP-24,Yes,DIR from U16 so SMS writes reach CPLD and FRAM
U7,1,SN74LVC8T245PWR,High data byte 3V3-to-5V translator,TSSOP-24,Yes,Disabled by U15 in SMS mode
U8,1,SN74LVC1G17DBVR,USB-present bus-disable buffer,SOT-23-5,Yes,Powered from CART_5V; require Ioff
U9,1,W25Q16JVSSIQ,2-MiB RP2350 QSPI boot flash,SOIC-8 5.3mm,Yes,Dedicated XIP device
U10,1,W25Q128JVSIQ,16-MiB USB staging SPI NOR,SOIC-8 5.3mm,Yes,Dedicated FAT16 volume
U11,1,TLV75533PDBVR,500mA 3.3V LDO,SOT-23-5,Yes,Input from SYS_5V
U12,1,TPD2EUSB30DRTR,USB D+/D- ESD protector,SOT-9/DRT,Yes,Place beside J2
U13,1,ATF1508ASV-15AU100,Instant-on SMS mapper and MD lock-on save decoder CPLD,TQFP-100 14x14mm,Yes,3.3V; fit/timing and pins are release gates
U14,1,SN74LVC8T245PWR,Secondary-control 5V-to-3V3 translator,TSSOP-24,Yes,Translates LWR MRES UWR AS and TIME
U15,1,SN74LVC2G32DCUR,Cascaded upper-data output-disable OR gates,VSSOP-8,Yes,Powered CART_5V; also disables U7 during MD odd-byte FRAM cycles
U16,1,SN74LVC1G04DBVR,Low-data direction inverter,SOT-23-5,Yes,Powered CART_5V; U6 DIR = NOT LWR_N
U17-U18,2,FM18W08-SG,32Kx8 nonvolatile SMS save FRAM each,SOIC-28 wide,Yes,64 KiB total; low/high halves use separate CPLD chip enables
U19,1,SN74LVC1T45DBVR,3V3-to-5V MD high-data-disable translator,SOT-23-6,Yes,VCCA=3V3 VCCB=CART_5V DIR high; Ioff and VCC isolation required
U20,1,FM18W08-SG,32Kx8 dedicated Sonic 3 lock-on save FRAM,SOIC-28 wide,Yes,Only 8 KiB is decoded at odd byte addresses $200001-$203FFF
J1,1,2x32 2.54mm card edge,Mega Drive cartridge edge,PCB gold fingers,Yes,Hard gold and bevel required
J2,1,USB4105-GF-A,USB-C USB2 receptacle,USB-C 16-pin with shell stakes,Yes,Device/UFP only
J3,1,2x5 1.27mm header,SWD debug and UART header,PinHeader 2x05 P1.27mm,Optional,DNP after production programming
J4,1,2x5 1.27mm header,CPLD JTAG programming header,PinHeader 2x05 P1.27mm,Yes,Keep accessible during prototype work
Y1,1,ABM8-272-T3,12MHz crystal,3.2x2.5mm 4-pad,Yes,Match RP2350 hardware-guide network
L1,1,AOTA-B201610S3R3-101-T,3.3uH polarised RP2350 core-regulator inductor,2.0x1.6mm vendor footprint,Yes,Copy orientation and placement from current official design
F1,1,MF-MSMF020-2,200mA resettable fuse,1812,Yes,Revalidate against measured dual-system current
D1-D2,2,PMEG2010AEB,1A low-drop Schottky,SOD-523,Yes,Source isolation into SYS_5V
D3-D5,3,LTST-C190KGKT/LTST-C190YKT/LTST-C190KRKT,Green amber red status LEDs,0603,Yes,Use separate current resistors
Q1-Q4,4,2N7002,Open-drain M3 VA21 VA22 and PAUSE pulls,SOT-23,Yes,Gates never connect directly to 5V bus
R1-R2,2,5.1k 1%,USB-C CC1 and CC2 Rd,0603,Yes,One resistor per CC pin
R3-R4,2,27R 1%,USB D+/D- series resistors,0603,Yes,Place near U1
R5,1,10k,USB_VBUS to U8 input series resistor,0603,Yes,
R6,1,100k,U8 input pulldown,0603,Yes,
R7-R8,2,100k,USB detect and PROGRAM ADC divider,0603,Yes,GPIO44 sees VBUS/2; SW1 parallels R8
R9-R11,3,1k,LED current resistors,0603,Yes,
R12,1,10k,ROM_WE_N pullup,0603,Yes,Prevents accidental active-NOR writes
R13,1,0R,/CART strap to GND,0603,Yes,
R14,1,100k,BUS_DISABLE pulldown,0603,Yes,Keeps pass-through enabled during CART_5V ramp
R15-R18,4,10k,Optional translator OE pulldowns,0603,DNP,Common BUS_DISABLE is authoritative
R19-R23,5,10k,Translator DIR straps,0603,Yes,U3-U5/U14 high and U7 low; U6 is dynamic
R24,1,33R 1%,RP2350 VREG_AVDD filter resistor,0603,Yes,Confirm against current official reference
R25-R27,3,10k,Parallel-flash RESET/WP/mode straps,0603,Yes,Confirm names and polarities for exact package
R28,1,1k 1%,RP2350 crystal series resistor,0402/0603,Yes,Copy official position and connection
R29-R30,2,100k,Independent USB_MODE_3V3 divider,0603,Yes,USB_VBUS/2 to U13; never share PROGRAM button node
R31-R32,2,10k,ROM CE/OE inactive pullups,0603,Yes,Holds NOR inactive whenever U13 releases outputs
R33,1,10k,FRAM A14 pulldown,0603,Yes,Defaults address low whenever U13 releases output
R34-R36,3,10k,Low FRAM CE plus shared OE/WE inactive pullups,0603,Yes,Holds U17 and shared controls inactive
R37-R40,4,100k,Open-drain FET gate pulldowns,0603,Yes,MD and PAUSE default inactive
R41,1,100k,MRES_3V3 reset pulldown,0603,Yes,CPLD mapper defaults held until console reset arrives
R42,1,10k,FRAM A13 pulldown,0603,Yes,Defaults address low whenever U13 releases output
R43,1,10k,High FRAM CE inactive pullup,0603,Yes,Holds U18 inactive whenever U13 releases output
R44,1,100k,SW4 profile-select pulldown,0603,Yes,Defaults to Sega in SMS mode and linear/no-save in MD mode
R45,1,10k,Dedicated MD FRAM CE inactive pullup,0603,Yes,Holds U20 inactive whenever U13 releases output
C1-C18,18,100nF X7R,Local digital decoupling,0603,Yes,One at every IC rail pair plus MCU groups
C19-C22,4,1uF X7R,Bulk/local decoupling,0603,Yes,Flash CPLD and translator banks
C23-C24,2,10uF X7R,Regulator input/output bulk,0805,Yes,Check LDO stability guidance
C25-C26,2,15pF C0G 5%,Crystal load capacitors,0402/0603,Yes,Recalculate for layout and specified crystal
C27,1,4.7uF X7R,RP2350 1V1 core output capacitor,0603,Yes,Copy current official design
C28-C33,6,TBD per official reference,RP2350 regulator ADC and IO support capacitors,0402/0603,Yes,Do not release until copied from current minimal design
C34,1,100nF X7R,U18 local decoupling,0603,Yes,Place at U18 VDD
C35-C36,2,100nF X7R,U19 and U20 local decoupling,0603,Yes,Place at each new device supply
SW1,1,PTS636,Manual PROGRAM button,SMD 6x3.5mm,Yes,Pulls GPIO44 ADC ladder low only while USB mounted
SW2,1,DPDT break-before-make slide,MD/SMS hardware mode switch,SMD right-angle slide,Yes,One pole 3V3 mode/FET gates; one pole 5V U7 disable
SW3,1,PTS636,Master System PAUSE button,SMD 6x3.5mm,Yes,Drives Q4 gate only from SMS_MODE_3V3
SW4,1,SPDT break-before-make slide,SMS mapper / MD lock-on-save profile selector,SMD right-angle slide,Yes,Low=SEGA or LINEAR; high=CODEMASTERS or S3 SAVE; move only unpowered
TP1-TP22,22,Test points,Power mode bus mapper and lock-on diagnostics,1.0mm SMD pad,Yes,Include USB_MODE MD_FRAM_CE and MD_HIGH_DISABLE

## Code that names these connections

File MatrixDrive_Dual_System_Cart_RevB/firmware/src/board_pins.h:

/* SPDX-License-Identifier: MIT */
#pragma once

/* Parallel active-ROM bus: GPIO0..20 address, GPIO21..36 data. */
#define PIN_ROM_A_FIRST       0u
#define PIN_ROM_A_COUNT      21u
#define PIN_ROM_D_FIRST      21u
#define PIN_ROM_D_COUNT      16u
#define PIN_ROM_CE_N         37u
#define PIN_ROM_OE_N         38u
#define PIN_ROM_WE_N         39u

/* Dedicated SPI1 staging flash on the valid RP2350B GPIO40..43 group. */
#define PIN_STAGE_MISO       40u
#define PIN_STAGE_CS_N       41u
#define PIN_STAGE_SCK        42u
#define PIN_STAGE_MOSI       43u

/* GPIO44/ADC4 sits at about VBUS/2. SW1 pulls it low. */
#define PIN_USB_PROGRAM_ADC  44u
#define ADC_USB_PROGRAM_CH    4u
#define PIN_LED_GREEN        45u
#define PIN_LED_AMBER        46u
#define PIN_LED_RED          47u

#define STAGE_FLASH_BYTES    (16u * 1024u * 1024u)
#define MSC_BLOCK_BYTES      512u
#define MSC_BLOCK_COUNT      (STAGE_FLASH_BYTES / MSC_BLOCK_BYTES)
#define ACTIVE_ROM_BYTES     (4u * 1024u * 1024u)
#define ACTIVE_SMS_BYTES     (2u * 1024u * 1024u)
